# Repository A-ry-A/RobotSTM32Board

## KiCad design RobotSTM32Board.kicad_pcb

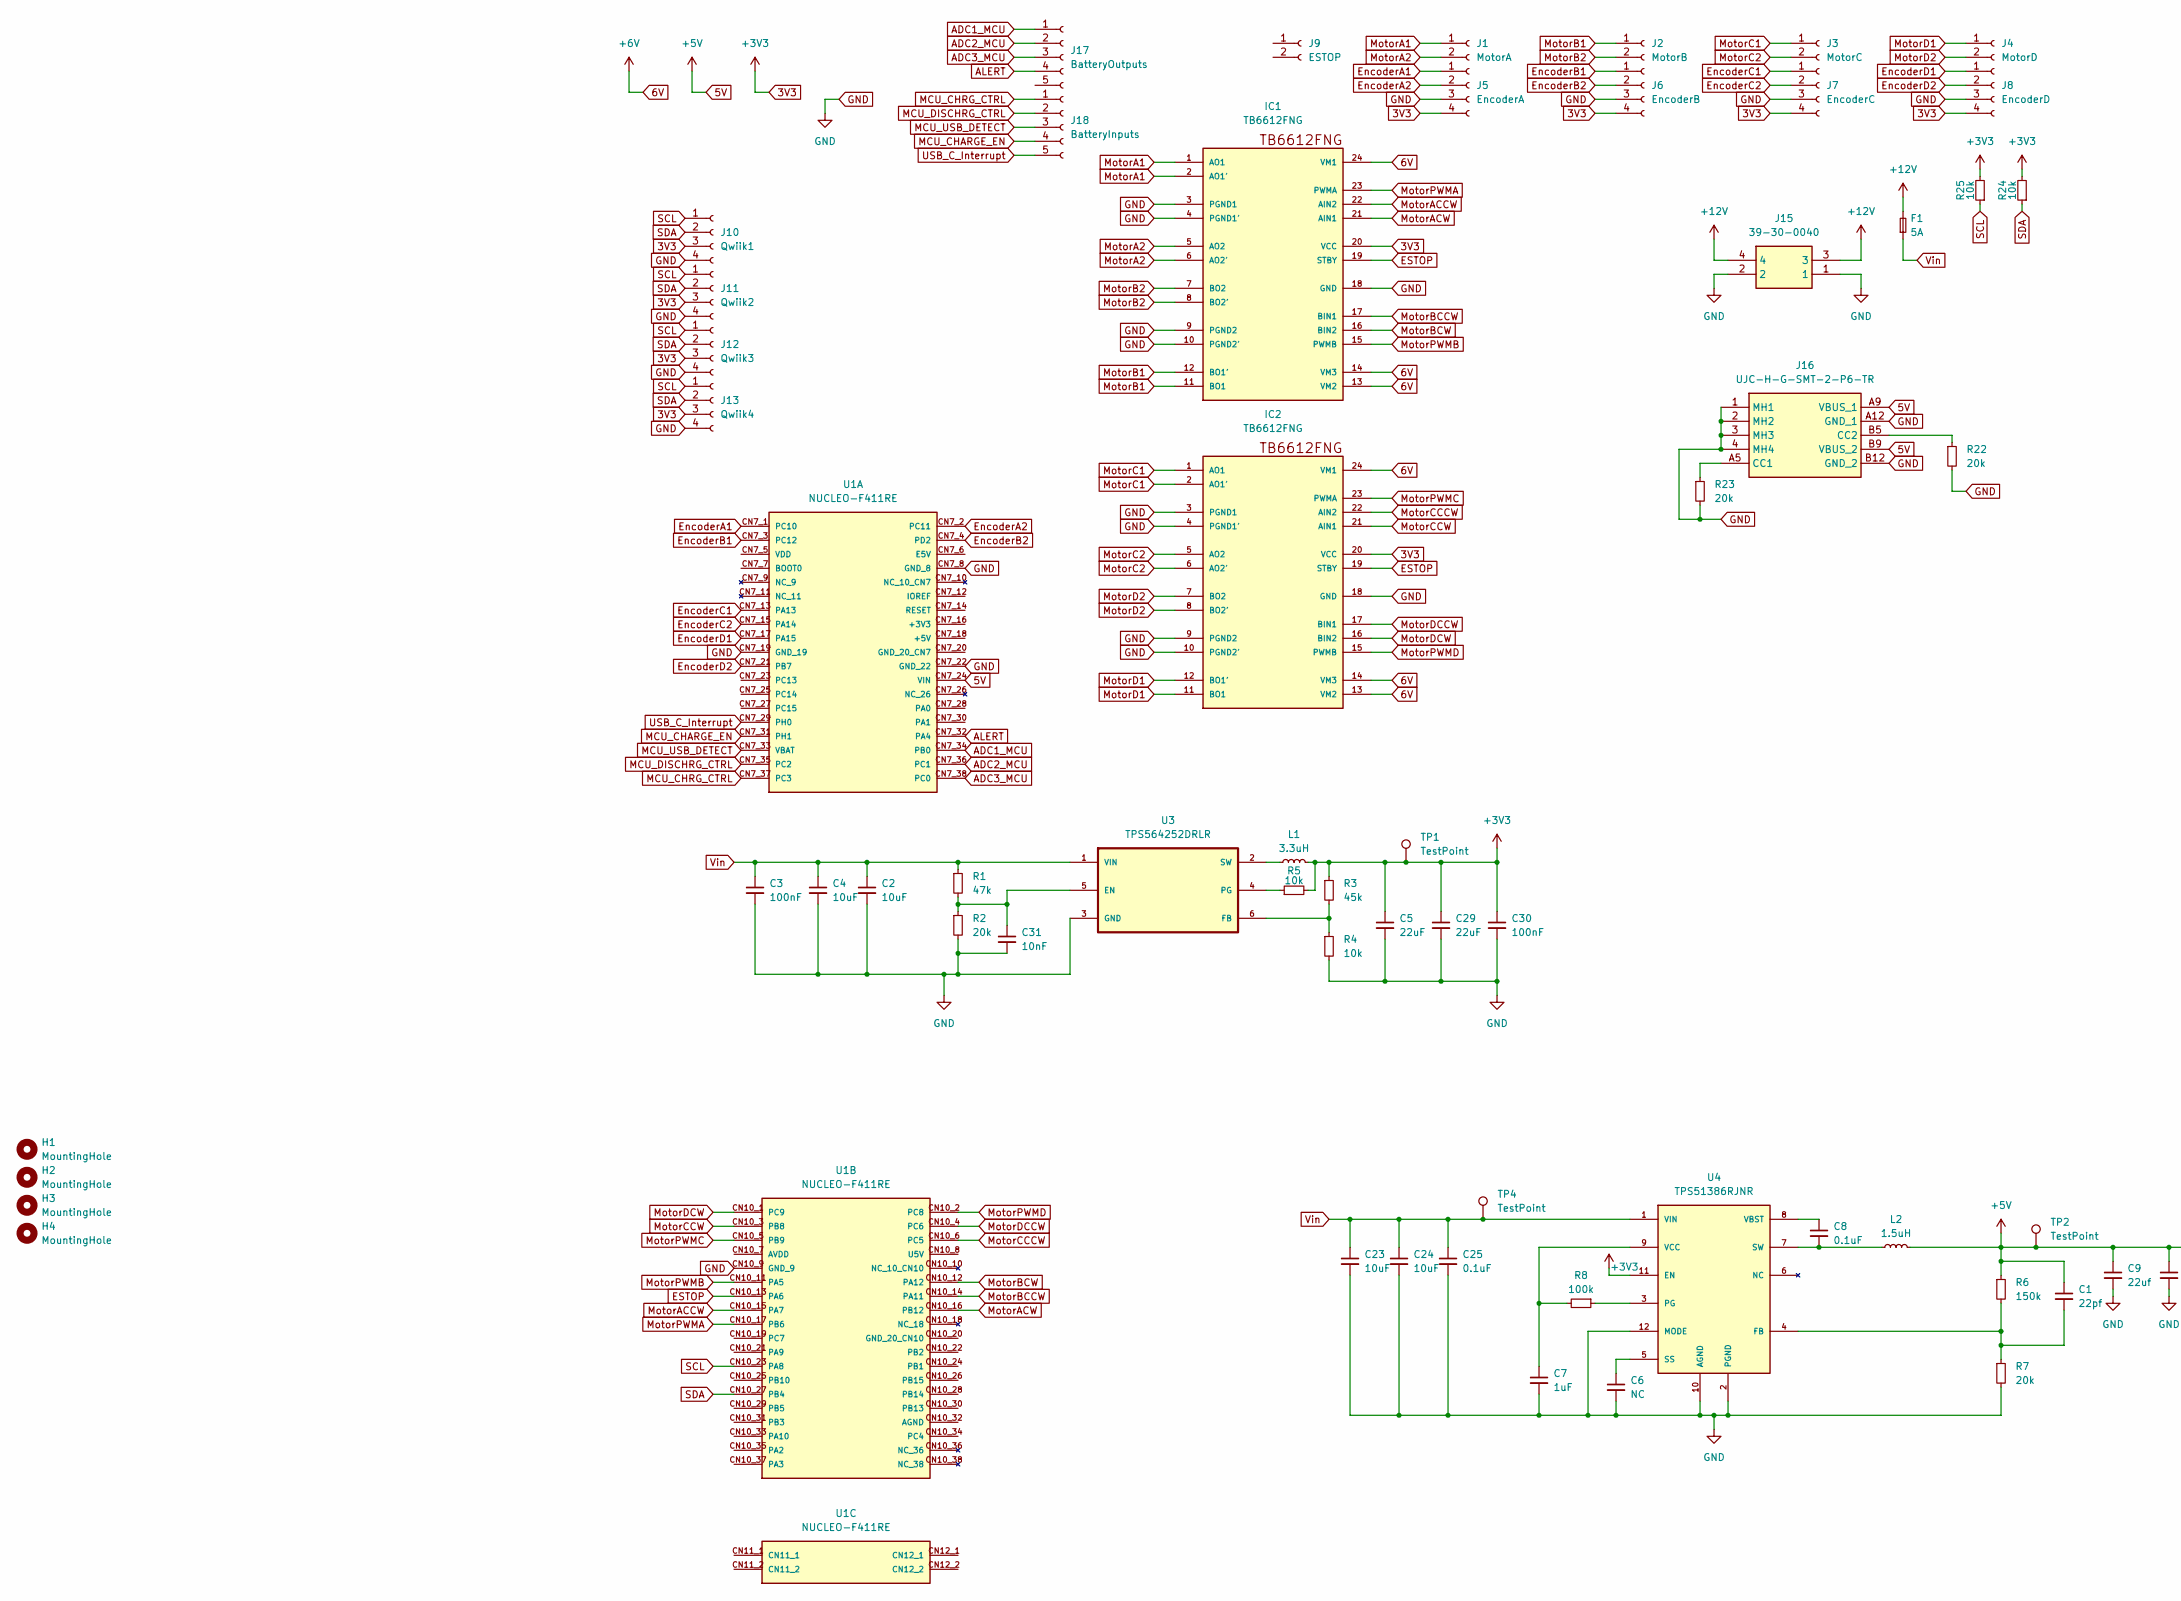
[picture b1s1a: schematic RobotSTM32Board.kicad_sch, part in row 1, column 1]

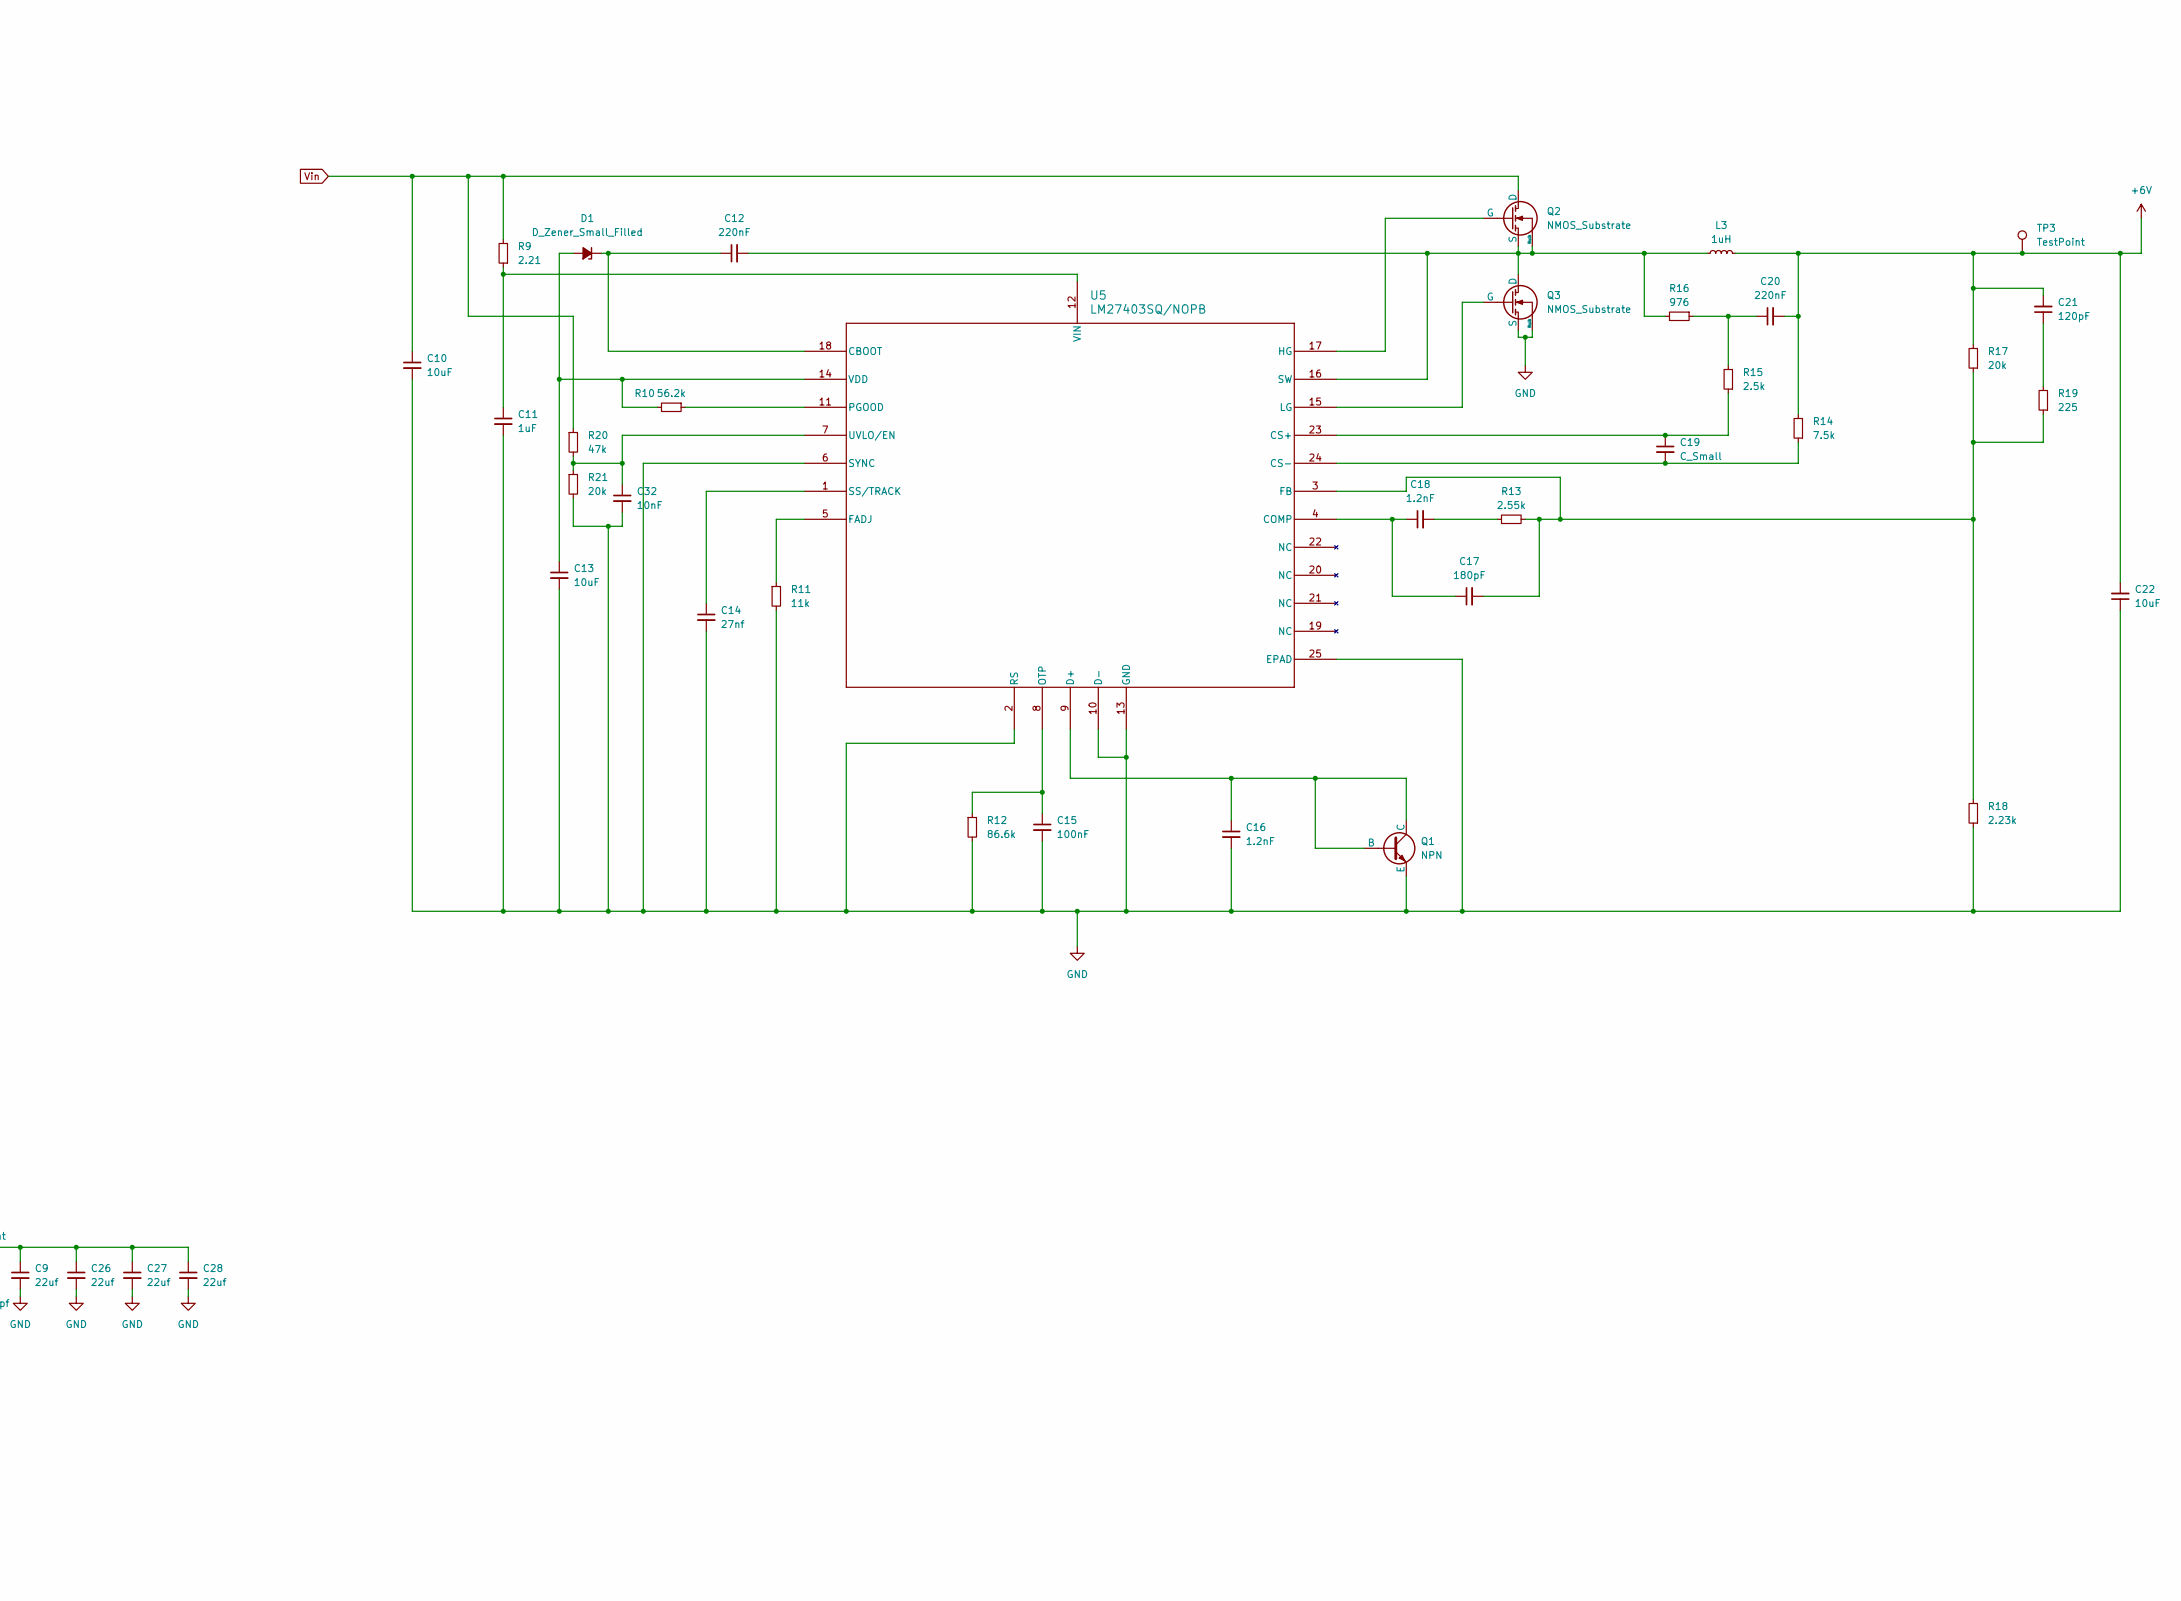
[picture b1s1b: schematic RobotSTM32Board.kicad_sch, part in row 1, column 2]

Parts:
C1: 22pf; C_0603_1608Metric
C2, C4, C10, C13, C22, C23, C24: 10uF; C_0603_1608Metric
C3, C15, C30: 100nF; C_0603_1608Metric
C5, C29: 22uF; C_0603_1608Metric
C6: NC; C_0603_1608Metric
C7, C11: 1uF; C_0603_1608Metric
C8, C25: 0.1uF; C_0603_1608Metric
C9, C26, C27, C28: 22uf; C_0603_1608Metric
C12, C20: 220nF; C_0603_1608Metric
C14: 27nf; C_0603_1608Metric
C16, C18: 1.2nF; C_0603_1608Metric
C17: 180pF; C_0603_1608Metric
C19: C_Small; C_0603_1608Metric
C21: 120pF; C_0603_1608Metric
C31, C32: 10nF; C_0603_1608Metric
D1: D_Zener_Small_Filled; D_0603_1608Metric
F1: 5A; R_0603_1608Metric
H1, H2, H3, H4: MountingHole; MountingHole_2.5mm
IC1, IC2: TB6612FNG; SSOP24
J1: MotorA; JST_XH_B2B-XH-AM_1x02_P2.50mm_Vertical
J2: MotorB; JST_XH_B2B-XH-AM_1x02_P2.50mm_Vertical
J3: MotorC; JST_XH_B2B-XH-AM_1x02_P2.50mm_Vertical
J4: MotorD; JST_XH_B2B-XH-AM_1x02_P2.50mm_Vertical
J5: EncoderA; JST_XH_B4B-XH-AM_1x04_P2.50mm_Vertical
J6: EncoderB; JST_XH_B4B-XH-AM_1x04_P2.50mm_Vertical
J7: EncoderC; JST_XH_B4B-XH-AM_1x04_P2.50mm_Vertical
J8: EncoderD; JST_XH_B4B-XH-AM_1x04_P2.50mm_Vertical
J9: ESTOP; JST_XH_B2B-XH-AM_1x02_P2.50mm_Vertical
J10: Qwiik1; JST_SH_BM04B-SRSS-TB_1x04-1MP_P1.00mm_Vertical
J11: Qwiik2; JST_SH_BM04B-SRSS-TB_1x04-1MP_P1.00mm_Vertical
J12: Qwiik3; JST_SH_BM04B-SRSS-TB_1x04-1MP_P1.00mm_Vertical
J13: Qwiik4; JST_SH_BM04B-SRSS-TB_1x04-1MP_P1.00mm_Vertical
J15: 39-30-0040; 39-30-Y040; Mouser Part Number 538-39-30-0040
J16: UJC-H-G-SMT-2-P6-TR; UJCHGSMT2P6TR; Mouser Part Number 179-UJCHGSMT2P6TR
J17: BatteryOutputs; JST_SH_BM05B-SRSS-TB_1x05-1MP_P1.00mm_Vertical
J18: BatteryInputs; JST_SH_BM05B-SRSS-TB_1x05-1MP_P1.00mm_Vertical
L1: 3.3uH; L_Bourns_SRN6045TA
L2: 1.5uH; L_Bourns_SRN6045TA
L3: 1uH; L_Bourns_SRN6045TA
Q1: NPN; SOT-23
Q2, Q3: NMOS_Substrate; TO-252-2_TabPin1
R1, R20: 47k; R_0603_1608Metric
R2, R7, R17, R21, R22, R23: 20k; R_0603_1608Metric
R3: 45k; R_0603_1608Metric
R4, R5, R24, R25: 10k; R_0603_1608Metric
R6: 150k; R_0603_1608Metric
R8: 100k; R_0603_1608Metric
R9: 2.21; R_0603_1608Metric
R10: 56.2k; R_0603_1608Metric
R11: 11k; R_0603_1608Metric
R12: 86.6k; R_0603_1608Metric
R13: 2.55k; R_0603_1608Metric
R14: 7.5k; R_0603_1608Metric
R15: 2.5k; R_0603_1608Metric
R16: 976; R_0603_1608Metric
R18: 2.23k; R_0603_1608Metric
R19: 225; R_0603_1608Metric
TP1, TP2, TP3, TP4: TestPoint
U1: NUCLEO-F411RE; BOARD_NUCLEO-F411RE; PARTREV 14
U3: TPS564252DRLR; SOT50P160X60-6N
U4: TPS51386RJNR; VREG_TPS51386RJNR; PARTREV *
U5: LM27403SQ/NOPB; RTW24

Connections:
3V3: C5.1, C29.1, C30.1, IC1.20 (VCC), IC2.20 (VCC), J5.4, J6.4, J7.4, J8.4, J10.3, J11.3, J12.3, J13.3, L1.2, R3.1, R5.2, R24.2, R25.2, TP1.1, U4.11 (EN)
5V: C1.1, C9.1, C26.1, C27.1, C28.1, J16.A9 (VBUS_1), J16.B9 (VBUS_2), L2.2, R6.1, TP2.1, U1.CN7_24 (VIN)
6V: C20.2, C21.2, C22.2, IC1.13 (VM2), IC1.14 (VM3), IC1.24 (VM1), IC2.13 (VM2), IC2.14 (VM3), IC2.24 (VM1), L3.2, R14.2, R17.2, TP3.1
+12V: F1.2, J15.3, J15.4
ADC1_MCU: J17.1, U1.CN7_34 (PB0)
ADC2_MCU: J17.2, U1.CN7_36 (PC1)
ADC3_MCU: J17.3, U1.CN7_38 (PC0)
ALERT: J17.4, U1.CN7_32 (PA4)
ESTOP: IC1.19 (STBY), IC2.19 (STBY), U1.CN10_13 (PA6)
EncoderA1: J5.1, U1.CN7_1 (PC10)
EncoderA2: J5.2, U1.CN7_2 (PC11)
EncoderB1: J6.1, U1.CN7_3 (PC12)
EncoderB2: J6.2, U1.CN7_4 (PD2)
EncoderC1: J7.1, U1.CN7_13 (PA13)
EncoderC2: J7.2, U1.CN7_15 (PA14)
EncoderD1: J8.1, U1.CN7_17 (PA15)
EncoderD2: J8.2, U1.CN7_21 (PB7)
GND: C2.2, C3.2, C4.2, C5.2, C6.2, C7.2, C9.2, C10.2, C11.2, C13.2, C14.2, C15.2, C16.2, C22.1, C23.2, C24.2, C25.2, C26.2, C27.2, C28.2, C29.2, C30.2, C31.2, C32.2, IC1.3 (PGND1), IC1.4 (PGND1'), IC1.9 (PGND2), IC1.10 (PGND2'), IC1.18 (GND), IC2.3 (PGND1), IC2.4 (PGND1'), IC2.9 (PGND2), IC2.10 (PGND2'), IC2.18 (GND), J5.3, J6.3, J7.3, J8.3, J10.4, J11.4, J12.4, J13.4, J15.1, J15.2, J16.1 (MH1), J16.2 (MH2), J16.3 (MH3), J16.4 (MH4), J16.A12 (GND_1), J16.B12 (GND_2), Q1.3 (E), Q3.3 (S), Q3.4 (Bulk), R2.2, R4.2, R7.2, R11.2, R12.2, R18.1, R21.2, R22.2, R23.2, U1.CN7_8 (GND_8), U1.CN7_19 (GND_19), U1.CN7_22 (GND_22), U1.CN10_9 (GND_9), U3.3 (GND), U4.2 (PGND), U4.10 (AGND), U4.12 (MODE), U5.2 (RS), U5.6 (SYNC), U5.10 (D-), U5.13 (GND), U5.25 (EPAD)
MCU_CHARGE_EN: J18.4, U1.CN7_31 (PH1)
MCU_CHRG_CTRL: J18.1, U1.CN7_37 (PC3)
MCU_DISCHRG_CTRL: J18.2, U1.CN7_35 (PC2)
MCU_USB_DETECT: J18.3, U1.CN7_33 (VBAT)
MotorA1: IC1.1 (AO1), IC1.2 (AO1'), J1.1
MotorA2: IC1.5 (AO2), IC1.6 (AO2'), J1.2
MotorACCW: IC1.22 (AIN2), U1.CN10_15 (PA7)
MotorACW: IC1.21 (AIN1), U1.CN10_16 (PB12)
MotorB1: IC1.11 (BO1), IC1.12 (BO1'), J2.1
MotorB2: IC1.7 (BO2), IC1.8 (BO2'), J2.2
MotorBCCW: IC1.17 (BIN1), U1.CN10_14 (PA11)
MotorBCW: IC1.16 (BIN2), U1.CN10_12 (PA12)
MotorC1: IC2.1 (AO1), IC2.2 (AO1'), J3.1
MotorC2: IC2.5 (AO2), IC2.6 (AO2'), J3.2
MotorCCCW: IC2.22 (AIN2), U1.CN10_6 (PC5)
MotorCCW: IC2.21 (AIN1), U1.CN10_3 (PB8)
MotorD1: IC2.11 (BO1), IC2.12 (BO1'), J4.1
MotorD2: IC2.7 (BO2), IC2.8 (BO2'), J4.2
MotorDCCW: IC2.17 (BIN1), U1.CN10_4 (PC6)
MotorDCW: IC2.16 (BIN2), U1.CN10_1 (PC9)
MotorPWMA: IC1.23 (PWMA), U1.CN10_17 (PB6)
MotorPWMB: IC1.15 (PWMB), U1.CN10_11 (PA5)
MotorPWMC: IC2.23 (PWMA), U1.CN10_5 (PB9)
MotorPWMD: IC2.15 (PWMB), U1.CN10_2 (PC8)
unnamed: C18.2, R13.1
unnamed: C20.1, R15.2, R16.1
unnamed: C21.1, R19.2
unnamed: C13.1, D1.2 (A), R10.2, U5.14 (VDD)
unnamed: C12.1, D1.1 (K), U5.18 (CBOOT)
unnamed: J16.A5 (CC1), R23.1
unnamed: J16.B5 (CC2), R22.1
unnamed: C16.1, Q1.1 (C), Q1.2 (B), U5.9 (D+)
unnamed: C12.2, L3.1, Q2.3 (S), Q2.4 (Bulk), Q3.1 (D), R16.2, U5.16 (SW)
unnamed: Q2.2 (G), U5.17 (HG)
unnamed: Q3.2 (G), U5.15 (LG)
unnamed: C31.1, R1.2, R2.1, U3.5 (EN)
unnamed: R3.2, R4.1, U3.6 (FB)
unnamed: R5.1, U3.4 (PG)
unnamed: L1.1, U3.2 (SW)
unnamed: C1.2, R6.2, R7.1, U4.4 (FB)
unnamed: R8.1, U4.3 (PG)
unnamed: C6.1, U4.5 (SS)
unnamed: C8.2, L2.1, U4.7 (SW)
unnamed: C8.1, U4.8 (VBST)
unnamed: C7.1, R8.2, U4.9 (VCC)
unnamed: C17.1, C18.1, U5.4 (COMP)
unnamed: C19.1, R15.1, U5.23 (CS+)
unnamed: C19.2, R14.1, U5.24 (CS-)
unnamed: R11.1, U5.5 (FADJ)
unnamed: C17.2, R13.2, R17.1, R18.2, R19.1, U5.3 (FB)
unnamed: C15.1, R12.1, U5.8 (OTP)
unnamed: R10.1, U5.11 (PGOOD)
unnamed: C14.1, U5.1 (SS/TRACK)
unnamed: C32.1, R20.2, R21.1, U5.7 (UVLO/EN)
unnamed: C11.1, R9.1, U5.12 (VIN)
SCL: J10.1, J11.1, J12.1, J13.1, R25.1, U1.CN10_23 (PA8)
SDA: J10.2, J11.2, J12.2, J13.2, R24.1, U1.CN10_27 (PB4)
USB_C_Interrupt: J18.5, U1.CN7_29 (PH0)
Vin: C2.1, C3.1, C4.1, C10.1, C23.1, C24.1, C25.1, F1.1, Q2.1 (D), R1.1, R9.2, R20.1, TP4.1, U3.1 (VIN), U4.1 (VIN)

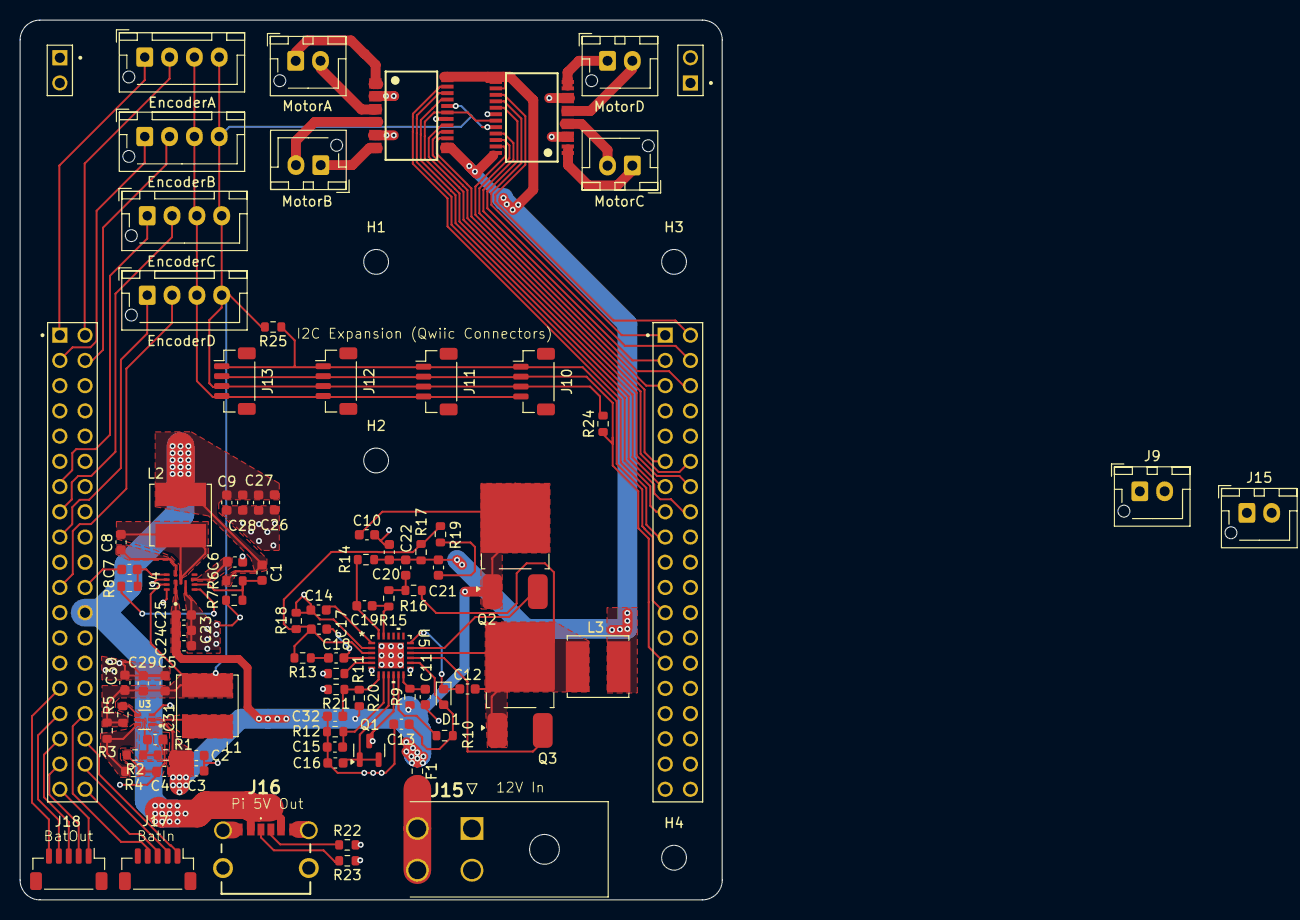
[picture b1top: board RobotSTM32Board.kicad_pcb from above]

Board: 2 copper layers, 70.7 x 88.6 mm, 93 parts (0 on the bottom side), 77 nets.

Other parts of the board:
J15#2: DCIn; JST_XH_B2B-XH-AM_1x02_P2.50mm_Vertical

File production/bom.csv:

Designator,Footprint,Quantity,Value,LCSC Part #
,,1,,
C1,0603,1,22pf,
"C10, C13, C2, C22, C23, C24, C4",0603,7,10uF,
"C11, C7",0603,2,1uF,
"C12, C20",0603,2,220nF,
C14,0603,1,27nf,
"C15, C3, C30",0603,3,100nF,
"C16, C18",0603,2,1.2nF,
C17,0603,1,180pF,
C19,0603,1,C_Small,
C21,0603,1,120pF,
"C25, C8",0603,2,0.1uF,
"C26, C27, C28, C29, C5, C9",0603,6,22uf,
"C31, C32",0603,2,10nF,
C6,0603,1,NC,
D1,0603,1,D_Zener_Small_Filled,
"IC1, IC2",SSOP24,2,TB6612FNG,
J1,JST_XH_B2B-XH-AM_1x02_P2.50mm_Vertical,1,MotorA,
J10,JST_SH_BM04B-SRSS-TB_1x04-1MP_P1.00mm_Vertical,1,Qwiik1,
J11,JST_SH_BM04B-SRSS-TB_1x04-1MP_P1.00mm_Vertical,1,Qwiik2,
J12,JST_SH_BM04B-SRSS-TB_1x04-1MP_P1.00mm_Vertical,1,Qwiik3,
J13,JST_SH_BM04B-SRSS-TB_1x04-1MP_P1.00mm_Vertical,1,Qwiik4,
J14,JST_SH_BM04B-SRSS-TB_1x04-1MP_P1.00mm_Vertical,1,Qwiik5,
J15_2,39-30-Y040,1,39-30-0040,
J15,JST_XH_B2B-XH-AM_1x02_P2.50mm_Vertical,1,DCIn,
J16,UJCHGSMT2P6TR,1,UJC-H-G-SMT-2-P6-TR,
J2,JST_XH_B2B-XH-AM_1x02_P2.50mm_Vertical,1,MotorB,
J3,JST_XH_B2B-XH-AM_1x02_P2.50mm_Vertical,1,MotorC,
J4,JST_XH_B2B-XH-AM_1x02_P2.50mm_Vertical,1,MotorD,
J5,JST_XH_B4B-XH-AM_1x04_P2.50mm_Vertical,1,EncoderA,
J6,JST_XH_B4B-XH-AM_1x04_P2.50mm_Vertical,1,EncoderB,
J7,JST_XH_B4B-XH-AM_1x04_P2.50mm_Vertical,1,EncoderC,
J8,JST_XH_B4B-XH-AM_1x04_P2.50mm_Vertical,1,EncoderD,
J9,JST_XH_B2B-XH-AM_1x02_P2.50mm_Vertical,1,ESTOP,
L1,L_Bourns_SRN6045TA,1,3.3uH,
L2,L_Bourns_SRN6045TA,1,1.5uH,
L3,L_Bourns_SRN6045TA,1,1uH,
Q1,SOT-23,1,NPN,
"Q2, Q3",TO-252-2_TabPin1,2,NMOS_Substrate,
"R1, R20",0603,2,47k,
R10,0603,1,56.2k,
R11,0603,1,11k,
R12,0603,1,86.6k,
R13,0603,1,2.55k,
R14,0603,1,7.5k,
R15,0603,1,2.5k,
R16,0603,1,976,
"R17, R2, R21, R22, R23, R7",0603,6,20k,
R18,0603,1,2.23k,
R19,0603,1,225,
R3,0603,1,45k,
"R4, R5",0603,2,10k,
R6,0603,1,150k,
R8,0603,1,100k,
R9,0603,1,2.21,
U1,BOARD_NUCLEO-F411RE,1,NUCLEO-F411RE,
U3,SOT50P160X60-6N,1,TPS564252DRLR,
U4,VREG_TPS51386RJNR,1,TPS51386RJNR,
U5,RTW24,1,LM27403SQ/NOPB,

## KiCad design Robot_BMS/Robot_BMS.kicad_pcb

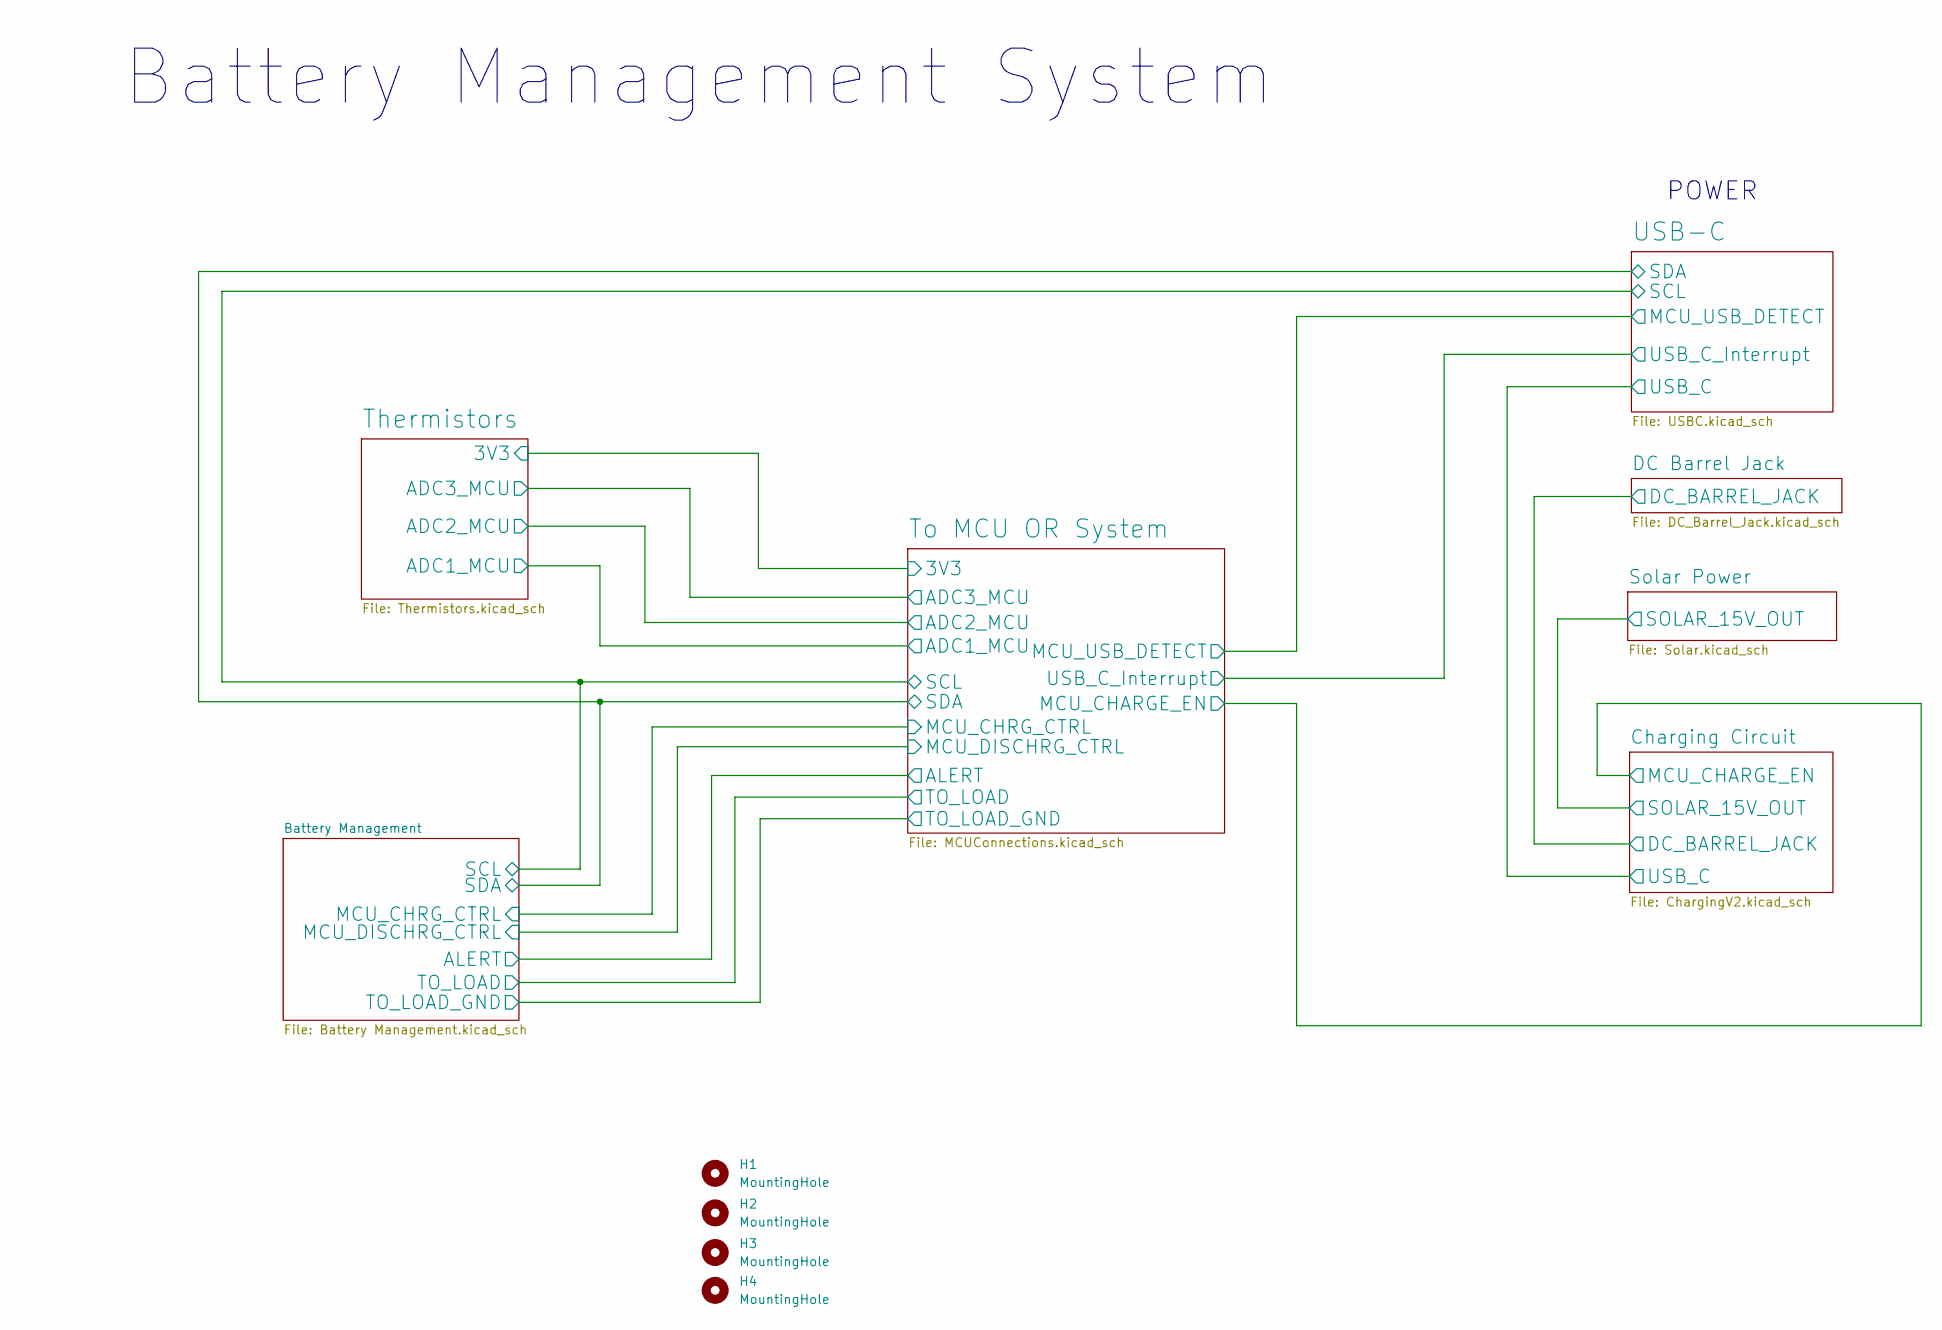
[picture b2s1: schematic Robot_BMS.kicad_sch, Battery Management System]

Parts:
H1, H2, H3, H4: MountingHole; MountingHole_2.5mm

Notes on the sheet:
POWER
Battery Management System

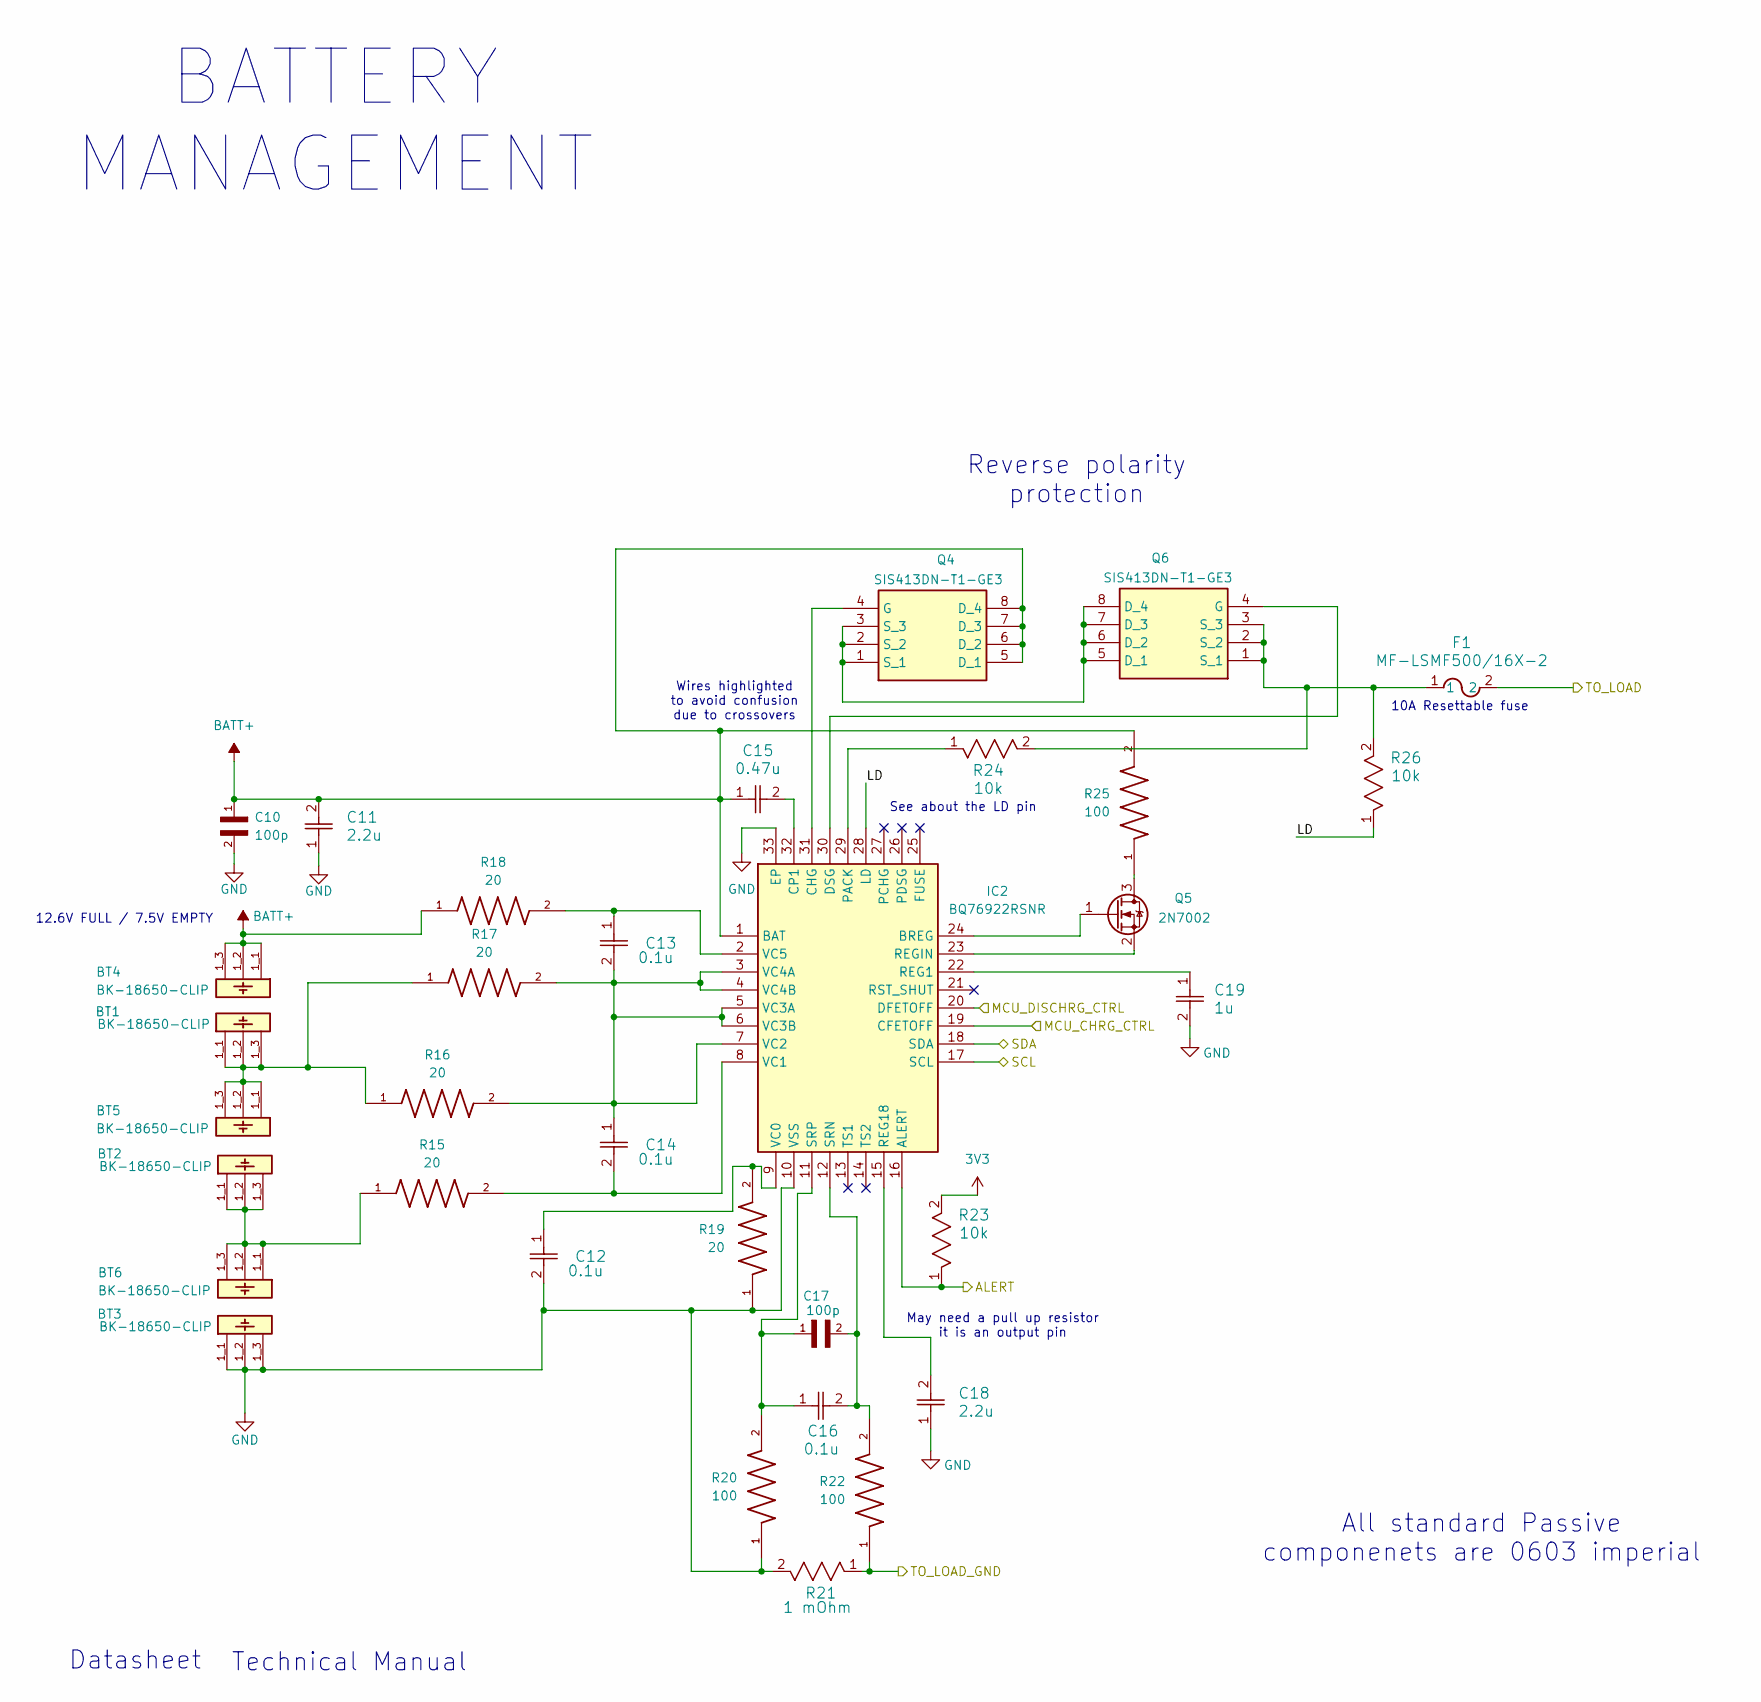
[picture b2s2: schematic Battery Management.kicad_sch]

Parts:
BT1, BT2, BT3, BT4, BT5, BT6: BK-18650-CLIP; BAT_BK-18650-CLIP; PARTREV A
C10, C17: 100p; CAPC1608X97N; Manufacturer_Part_Number GA0603A101JXBAC31G
C11, C18: 2.2u; CAP_GRM188R61H225KE11__MUR; Manufacturer_Part_Number GRM188R61H225KE11D
C12, C13, C14, C16: 0.1u; CAPC17595_87N_KEM; Manufacturer_Part_Number C0603C104K5RACAUTO
C15: 0.47u; CAP_1608_TDK; Manufacturer_Part_Number C1608X5R1H474K080AB
C19: 1u; CAP_1608_TDK; Manufacturer_Part_Number C1608X5R1H105K080AB
F1: MF-LSMF500/16X-2; FUSE_MF-LSMF185&slash_33X_BRN
IC2: BQ76922RSNR; QFN40P400X400X80-33N-D; Manufacturer_Part_Number BQ76922RSNR
Q4, Q6: SIS413DN-T1-GE3; SIS862DNT1GE3; Manufacturer_Part_Number SIS413DN-T1-GE3; Mouser Part Number 78-SIS413DN-T1-GE3
Q5: 2N7002; SOT-23; Manufacturer_Part_Number 2N7002 H6327
R15, R16, R17, R18, R19: 20; RES_ERJPA3F20R0V; PARTREV 3/1/2020
R20, R22, R25: 100; RESC1608X55N; PARTREV V6
R21: 1 mOhm; RC0603N_YAG; Manufacturer_Part_Number 580060716002
R23, R24, R26: 10k; RC0603N_YAG; Manufacturer_Part_Number RC0603FR-0710KL

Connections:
3V3: R23.2; also elsewhere on the board
/Battery Management/ALERT: IC2.16 (ALERT), R23.1; also elsewhere on the board
/Battery Management/LD: IC2.28 (LD), R26.1
/Battery Management/MCU_CHRG_CTRL: IC2.19 (CFETOFF); also elsewhere on the board
/Battery Management/MCU_DISCHRG_CTRL: IC2.20 (DFETOFF); also elsewhere on the board
/Battery Management/SCL: IC2.17 (SCL); also elsewhere on the board
/Battery Management/SDA: IC2.18 (SDA); also elsewhere on the board
/Battery Management/TO_LOAD: F1.2; also elsewhere on the board
/Battery Management/TO_LOAD_GND: R21.1, R22.1; also elsewhere on the board
BATT+: BT4.1_1, BT4.1_2, BT4.1_3, C10.1, C11.2, C15.1, IC2.1 (BAT), Q4.5 (D_1), Q4.6 (D_2), Q4.7 (D_3), Q4.8 (D_4), Q4.9, Q4.10, Q4.11, R18.1, R25.2
GND: BT3.1_1, BT3.1_2, BT3.1_3, C10.2, C11.1, C12.2, C18.1, C19.2, IC2.10 (VSS), IC2.33 (EP), R19.1, R20.1, R21.2; also elsewhere on the board
unnamed: BT1.1_1, BT1.1_2, BT1.1_3, BT5.1_1, BT5.1_2, BT5.1_3, R16.1, R17.1
unnamed: BT2.1_1, BT2.1_2, BT2.1_3, BT6.1_1, BT6.1_2, BT6.1_3, R15.1
unnamed: IC2.24 (BREG), Q5.1 (G)
unnamed: IC2.31 (CHG), Q4.4 (G)
unnamed: C15.2, IC2.32 (CP1)
unnamed: IC2.30 (DSG), Q6.4 (G)
unnamed: IC2.29 (PACK), R24.1
unnamed: C19.1, IC2.22 (REG1)
unnamed: C18.2, IC2.15 (REG18)
unnamed: IC2.23 (REGIN), Q5.2 (S)
unnamed: C16.2, C17.2, IC2.12 (SRN), R22.2
unnamed: C16.1, C17.1, IC2.11 (SRP), R20.2
unnamed: C12.1, IC2.9 (VC0), R19.2
unnamed: C14.2, IC2.8 (VC1), R15.2
unnamed: C13.2, C14.1, IC2.3 (VC4A), IC2.4 (VC4B), IC2.5 (VC3A), IC2.6 (VC3B), IC2.7 (VC2), R16.2, R17.2
unnamed: C13.1, IC2.2 (VC5), R18.2
unnamed: Q4.1 (S_1), Q4.2 (S_2), Q4.3 (S_3), Q6.5 (D_1), Q6.6 (D_2), Q6.7 (D_3), Q6.8 (D_4), Q6.9, Q6.10, Q6.11
unnamed: Q5.3 (D), R25.1
unnamed: F1.1, Q6.1 (S_1), Q6.2 (S_2), Q6.3 (S_3), R24.2, R26.2

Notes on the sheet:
Wires highlighted to avoid confusion due to crossovers
May need a pull up resistor it is an output pin
Reverse polarity protection
Technical Manual
Datasheet
BATTERY MANAGEMENT
12.6V FULL / 7.5V EMPTY
See about the LD pin
All standard Passive componenets are 0603 imperial
10A Resettable fuse
